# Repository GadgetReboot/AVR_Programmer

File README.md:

# AVR_Programmer
Atmel AVR programmer based on Arduino Pro Micro, intended for development into ISP and HVSP using various AVR programming interfaces and protocols.

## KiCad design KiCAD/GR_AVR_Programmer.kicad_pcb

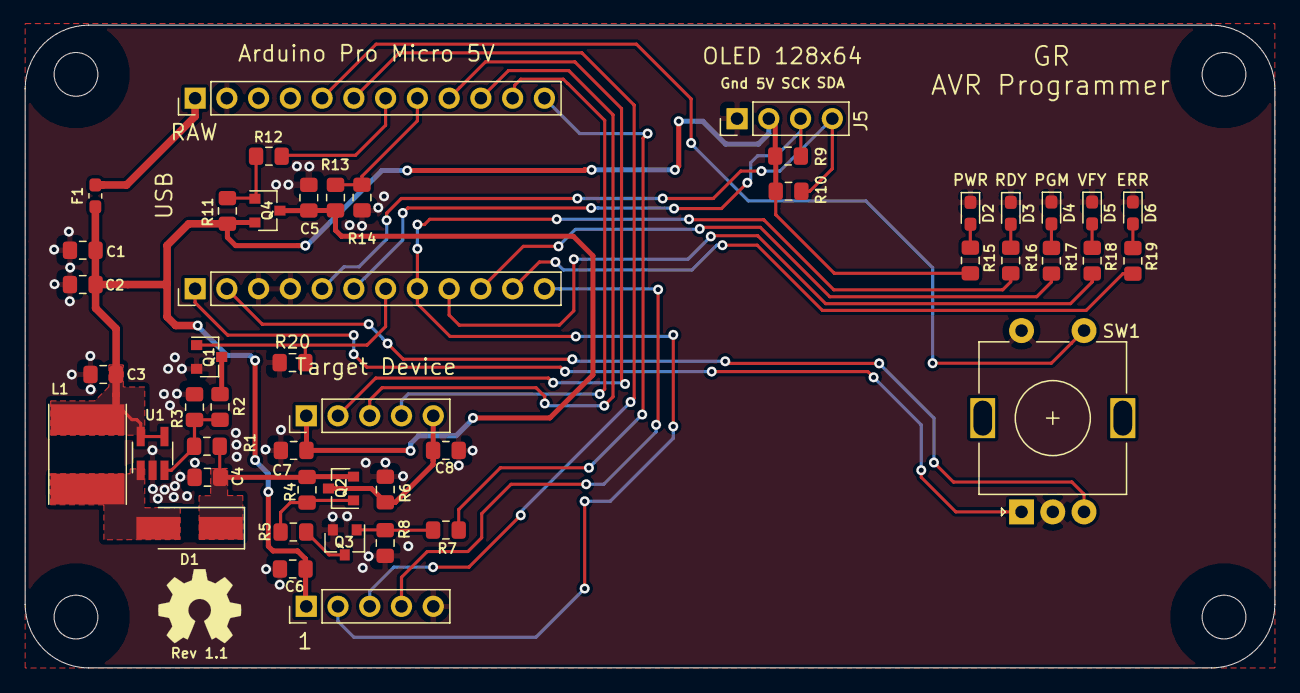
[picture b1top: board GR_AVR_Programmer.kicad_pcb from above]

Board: 2 copper layers, 99.9 x 51.4 mm, 47 parts (0 on the bottom side), 36 nets.

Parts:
C1, C3, C4: 4.7uF; C_0805_2012Metric_Pad1.15x1.40mm_HandSolder
C2, C5, C6, C7, C8: 100nF; C_0805_2012Metric_Pad1.15x1.40mm_HandSolder
D1: SK35; D_SMA_Handsoldering
D2, D3, D4, D5, D6: LED; LED_0603_1608Metric_Pad1.05x0.95mm_HandSolder
F1: PTC; Fuse_0603_1608Metric_Pad1.05x0.95mm_HandSolder
J1, J2: Conn_01x12; PinHeader_1x12_P2.54mm_Vertical
J3, J4: Conn_01x05; PinHeader_1x05_P2.54mm_Vertical
J5: Conn_01x04; PinHeader_1x04_P2.54mm_Vertical
L1: 22uH; L_Taiyo-Yuden_NR-60xx_HandSoldering
Q1: BSS138; SOT-23
Q2: MMBT3906; SOT-23
Q3: MMBT3904; SOT-23
Q4: BSS83P; SOT-23
R1, R4, R8, R11, R13, R20: 91K; R_0805_2012Metric_Pad1.15x1.40mm_HandSolder
R2: 16K; R_0805_2012Metric_Pad1.15x1.40mm_HandSolder
R3: 30K; R_0805_2012Metric_Pad1.15x1.40mm_HandSolder
R5, R7, R9, R10, R12: 10K; R_0805_2012Metric_Pad1.15x1.40mm_HandSolder
R6: 2K; R_0805_2012Metric_Pad1.15x1.40mm_HandSolder
R14: 56K; R_0805_2012Metric_Pad1.15x1.40mm_HandSolder
R15, R16, R17, R18, R19: 1K; R_0805_2012Metric_Pad1.15x1.40mm_HandSolder
SW1: Rotary_Encoder_Switch; RotaryEncoder_Alps_EC11E-Switch_Vertical_H20mm
U1: AP3012; SOT-23-5_HandSoldering

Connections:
/A2_D20: J2.6, J3.3
/ENC_A: J1.1, SW1.A
/ENC_B: J1.2, SW1.B
/ENC_SW: J2.5, SW1.S1
/ERR: J1.11, R19.1
/MISO_SII: J2.10, J4.3
/MOSI_SDI: J2.11, J4.4
/PGM: J1.10, R17.1
/RAW: F1.2, J2.1
/RDY: J1.8, J3.2, R16.1
/RST_EN: J2.12, R7.1
/SCI: J1.12, J3.4
/SCK: J1.6, J5.3, R9.1
/SCK_SDO: J2.9, J4.2
/SDA: J1.5, J5.4, R10.1
/TG_RST: C8.1, J4.5, Q2.3, R6.2
/VFY: J1.9, R18.1
/VRST: J1.7, Q1.1, R20.2
/VTG: C5.1, C7.1, J4.1, Q4.3, R13.2
/VTG_EN: J2.7, R12.1
/VTG_MON: J2.8, R13.1, R14.2
GNDREF: C1.2, C2.2, C3.2, C4.2, C5.2, C6.2, C7.2, C8.2, D2.1, D3.1, D4.1, D5.1, D6.1, J1.3, J1.4, J2.2, J3.5, J5.1, Q1.2, Q3.2, R3.1, R6.1, R8.1, R14.1, R20.1, SW1.C, SW1.S2, U1.2
unnamed: C4.1, D1.1, Q2.2, R1.2, R4.2
unnamed: D1.2, L1.2, U1.1
unnamed: D2.2, R15.2
unnamed: D3.2, R16.2
unnamed: D4.2, R17.2
unnamed: D5.2, R18.2
unnamed: D6.2, R19.2
unnamed: Q1.3, R2.1
unnamed: Q2.1, R4.1, R5.2
unnamed: Q3.1, R7.2, R8.2
unnamed: Q3.3, R5.1
unnamed: Q4.1, R11.1, R12.2
unnamed: R1.1, R2.2, R3.2, U1.3
VCC: C1.1, C2.1, C3.1, C6.1, F1.1, J3.1, J5.2, L1.1, Q4.2, R9.2, R10.2, R11.2, R15.1, U1.4, U1.5

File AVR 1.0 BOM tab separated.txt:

Ref. Des.	Qty	Value	Description	Manufacturer Example	P/N Example
			C1, C3, C4	3	4.7uF	CAP CER 4.7UF >=16V X7R 0805	Murata	GRM21BR71C475KE51L
			C2, C5-C8	5	100nF	CAP CER 0.1UF >=16V X7R 0805	Murata	GCM21BR71H104KA37K
			D1	1	SK35	DIODE SCHOTTKY 50V 3A SMA	Micro Commercial	SK35A-TP
			D2-D6	5	LED	LED SMD 0603 	 	 
			F1	1	PTC	PTC RESET FUSE 6V 500MA 0603	Bourns	MF-FSMF050X-2
			J1, J2	2	1x12 	Header 1x12 female 2.54mm pitch		 
			J3, J4	2	1x5	Header 1x5 female 2.54mm pitch		 
			J5	1	1x4	Header 1x4 female 2.54mm pitch		 
			L1	1	22uH	IND 22UH 1.9A SMD (can be 10uH or more, size 5x5mm or so)	Pulse	CDTH3D14/HPNP-100NC
			Q1	1	BSS138	MOSFET N-CH 50V 220MA SOT-23	On Semi	BSS138
			Q2	1	MMBT3906	PNP 40V 0.2A SOT-23	On Semi	MMBT3906
			Q3	1	MMBT3904	NPN 40V 0.2A SOT-23	On Semi	MMBT3904
			Q4	1	BSS83P	MOSFET P-CH 60V 0.33A SOT23	Infineon	BSS83PH6327XTSA1
			R1, R4, R8, R11, R13	5	91K	RES SMD 91K OHM 1% 1/8W 0805	Panasonic	ERJ-6ENF9102V
			R2	1	16K	RES SMD 16K OHM 1% 1/8W 0805	Panasonic	ERJ-6ENF1602V
			R3	1	30K	RES SMD 30K OHM 1% 1/8W 0805	Panasonic	ERJ-6ENF3002V
			R6	1	2K	RES SMD 2K OHM 1% 1/8W 0805 (can be >1%)	Panasonic	ERJ-6ENF2001V
			R5, R7, R9, R10, R12	5	10K	RES SMD 10K OHM 1% 1/8W 0805 (can be >1%)	Panasonic	ERJ-6ENF1002V
			R14	1	56K	RES SMD 56K OHM 1% 1/8W 0805	Panasonic	ERJ-6ENF5602V
			R15-R19	5	1K	RES SMD 1K OHM 1% 1/8W 0805 (can be >1%)	Panasonic	ERJ-6ENF1001V
			SW1	1	Rotary Enc	Alps EC11E series Rotary Encoder with Push Switch	Alps	EC11E*
			U1	1	AP3012	IC REG BOOST ADJ 500MA SOT23-5	Diodes Inc	AP3012KTR-G1

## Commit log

2019-12-09 Create AVR_Prog_HVSP_ATTiny_Fuses
